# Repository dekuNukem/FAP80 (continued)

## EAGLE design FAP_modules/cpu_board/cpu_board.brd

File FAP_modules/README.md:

Here are all the schematic file, board file, and firmware of FAP's individual boards. Please see corresponding folders for details.

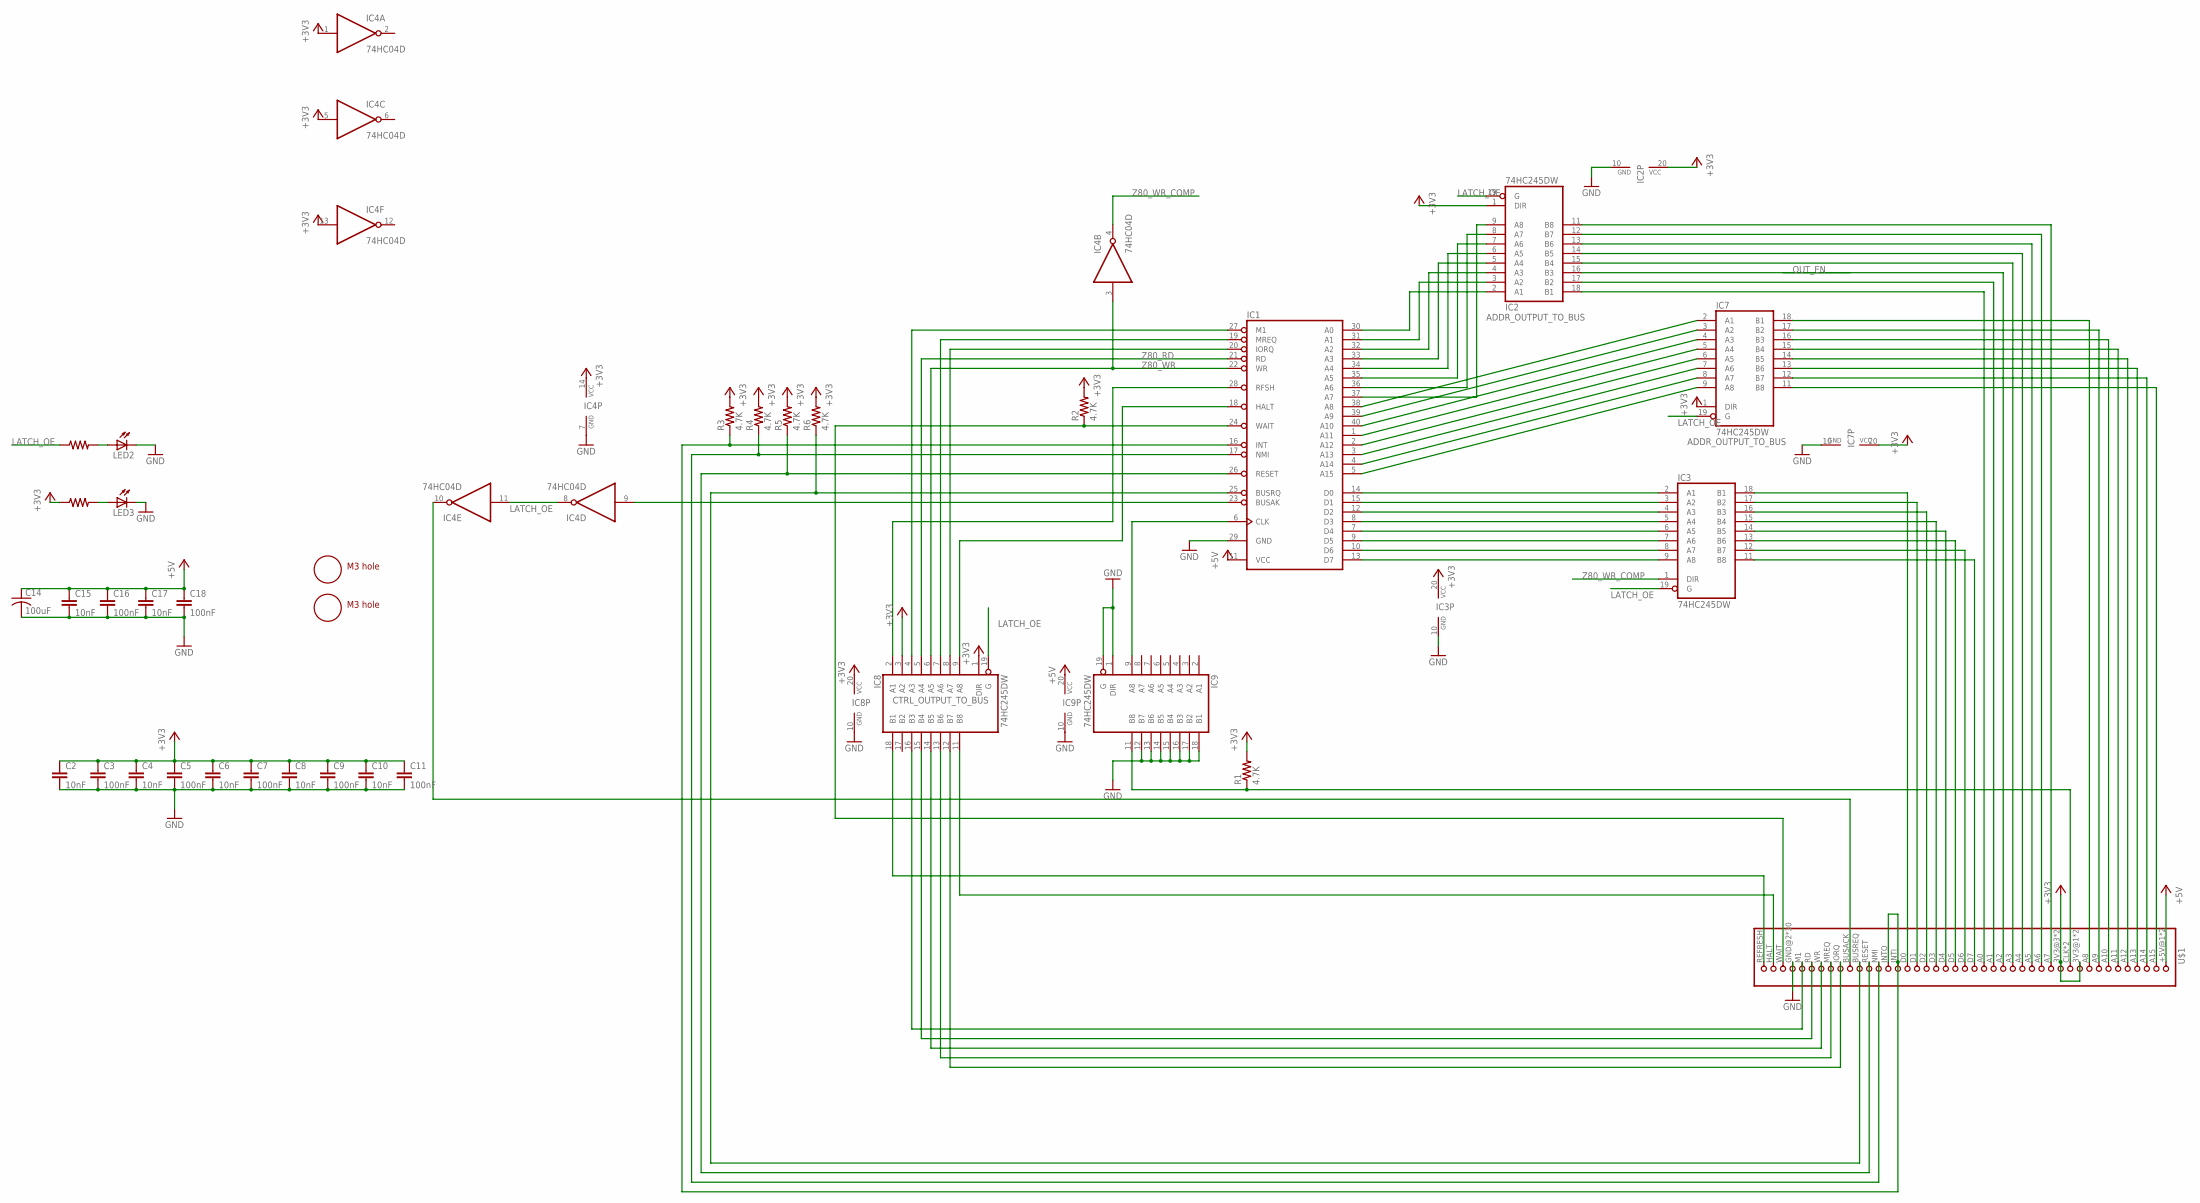
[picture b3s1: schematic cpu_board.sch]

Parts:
C2, C4, C6, C8, C10, C15, C17: 10nF; 0805
C3, C5, C7, C9, C11, C16, C18: 100nF; 0805
C14: 100uF; C1210
IC1: Z80CPU; DIL40
IC2, IC3, IC7, IC8, IC9: 74HC245DW; SO20W
IC4: 74HC04D; SO14
LED2, LED3: LEDCHIP-LED0805; CHIP-LED0805
R1, R2, R3, R4, R5, R6: 4.7K; 0805
R7, R8: 2K; 0805
U$1: FAP_BUS; 2X38
U$2, U$3: M3_MOUNTING_HOLE; M3_MOUNTING_HOLE_PACK

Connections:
+3V3: C2.1, C3.1, C4.1, C5.1, C6.1, C7.1, C8.1, C9.1, C10.1, C11.1, IC2.1 (DIR), IC2.20 (VCC), IC3.20 (VCC), IC4.1 (I), IC4.5 (I), IC4.13 (I), IC4.14 (VCC), IC7.1 (DIR), IC7.20 (VCC), IC8.1 (DIR), IC8.3 (A2), IC8.20 (VCC), R1.2, R2.2, R3.2, R4.2, R5.2, R6.2, R8.1, U$1.3V3@1 (10), U$1.3V3@2 (10), U$1.3V3@3 (12), U$1.3V3@4 (12)
+5V: C14.1, C15.1, C16.1, C17.1, C18.1, IC1.11 (VCC), IC9.20 (VCC), U$1.+5V@1 (1), U$1.+5V@2 (1)
GND: C2.2, C3.2, C4.2, C5.2, C6.2, C7.2, C8.2, C9.2, C10.2, C11.2, C14.2, C15.2, C16.2, C17.2, C18.2, IC1.29 (GND), IC2.10 (GND), IC3.10 (GND), IC4.7 (GND), IC7.10 (GND), IC8.10 (GND), IC9.1 (DIR), IC9.10 (GND), IC9.12 (B7), IC9.13 (B6), IC9.14 (B5), IC9.15 (B4), IC9.16 (B3), IC9.17 (B2), IC9.18 (B1), IC9.19 (G), LED2.C, LED3.C, U$1.GND@2 (GND), U$1.GND@3 (GND), U$1.GND@4 (GND), U$1.GND@5 (GND), U$1.GND@6 (GND), U$1.GND@7 (GND), U$1.GND@8 (GND), U$1.GND@9 (GND), U$1.GND@13 (GND), U$1.GND@14 (GND), U$1.GND@15 (GND), U$1.GND@16 (GND), U$1.GND@17 (GND), U$1.GND@18 (GND), U$1.GND@19 (GND), U$1.GND@20 (GND), U$1.GND@21 (GND), U$1.GND@22 (GND), U$1.GND@23 (GND), U$1.GND@24 (GND), U$1.GND@25 (GND), U$1.GND@26 (GND), U$1.GND@27 (GND), U$1.GND@28 (GND), U$1.GND@30 (GND), U$1.GND@34 (GND), U$1.GND@35 (GND), U$1.GND@36 (GND), U$1.GND@37 (GND), U$1.GND@38 (GND)
LATCH_OE: IC2.19 (G), IC3.19 (G), IC4.8 (O), IC4.11 (I), IC7.19 (G), IC8.19 (G), R7.1
unnamed: IC1.38 (A8), IC7.2 (A1)
unnamed: IC1.39 (A9), IC7.3 (A2)
unnamed: IC1.40 (A10), IC7.4 (A3)
unnamed: IC1.1 (A11), IC7.5 (A4)
unnamed: IC1.2 (A12), IC7.6 (A5)
unnamed: IC1.3 (A13), IC7.7 (A6)
unnamed: IC1.4 (A14), IC7.8 (A7)
unnamed: IC1.5 (A15), IC7.9 (A8)
unnamed: IC1.37 (A7), IC2.9 (A8)
unnamed: IC1.36 (A6), IC2.8 (A7)
unnamed: IC1.35 (A5), IC2.7 (A6)
unnamed: IC1.34 (A4), IC2.6 (A5)
unnamed: IC1.33 (A3), IC2.5 (A4)
unnamed: IC1.32 (A2), IC2.4 (A3)
unnamed: IC1.31 (A1), IC2.3 (A2)
unnamed: IC1.30 (A0), IC2.2 (A1)
unnamed: IC1.14 (D0), IC3.2 (A1)
unnamed: IC1.15 (D1), IC3.3 (A2)
unnamed: IC1.12 (D2), IC3.4 (A3)
unnamed: IC1.8 (D3), IC3.5 (A4)
unnamed: IC1.7 (D4), IC3.6 (A5)
unnamed: IC1.9 (D5), IC3.7 (A6)
unnamed: IC1.10 (D6), IC3.8 (A7)
unnamed: IC1.13 (D7), IC3.9 (A8)
unnamed: IC4.10 (O), U$1.BUSACK (33)
unnamed: IC9.11 (B8), R1.1, U$1.CLK (11), U$1.CLK@2 (11)
unnamed: IC1.6 (CLK), IC9.9 (A8)
unnamed: LED2.A, R7.2
unnamed: IC1.25 (BUSRQ), R6.1, U$1.BUSREQ (32)
unnamed: IC1.23 (BUSAK), IC4.9 (I)
unnamed: IC1.26 (RESET), R5.1, U$1.RESET (31)
unnamed: IC1.24 (WAIT), R2.1, U$1.WAIT (40)
unnamed: IC1.17 (NMI), R4.1, U$1.NMI (30)
unnamed: IC1.18 (HALT), IC8.9 (A8)
unnamed: IC1.16 (INT), R3.1, U$1.INTI (29), U$1.INTO (39)
unnamed: IC1.19 (MREQ), IC8.7 (A6)
unnamed: IC8.11 (B8), U$1.HALT (41)
unnamed: IC1.28 (RFSH), IC8.2 (A1)
unnamed: IC1.20 (IORQ), IC8.8 (A7)
unnamed: IC1.27 (M1), IC8.4 (A3)
unnamed: IC8.16 (B3), U$1.M1 (38)
unnamed: IC8.13 (B6), U$1.MREQ (35)
unnamed: IC8.15 (B4), U$1.RD (37)
unnamed: IC8.14 (B5), U$1.WR (36)
unnamed: IC8.12 (B7), U$1.IORQ (34)
unnamed: IC3.17 (B2), U$1.D1 (27)
unnamed: IC3.11 (B8), U$1.D7 (21)
unnamed: IC3.12 (B7), U$1.D6 (22)
unnamed: IC3.13 (B6), U$1.D5 (23)
unnamed: IC3.14 (B5), U$1.D4 (24)
unnamed: IC3.15 (B4), U$1.D3 (25)
unnamed: IC3.16 (B3), U$1.D2 (26)
unnamed: IC3.18 (B1), U$1.D0 (28)
unnamed: IC7.11 (B8), U$1.A15 (2)
unnamed: IC7.12 (B7), U$1.A14 (3)
unnamed: IC7.13 (B6), U$1.A13 (4)
unnamed: IC2.18 (B1), U$1.A0 (20)
unnamed: IC2.17 (B2), U$1.A1 (19)
unnamed: IC2.16 (B3), U$1.A2 (18)
unnamed: IC2.15 (B4), U$1.A3 (17)
unnamed: IC2.14 (B5), U$1.A4 (16)
unnamed: IC2.13 (B6), U$1.A5 (15)
unnamed: IC2.12 (B7), U$1.A6 (14)
unnamed: IC2.11 (B8), U$1.A7 (13)
unnamed: IC7.14 (B5), U$1.A12 (5)
unnamed: IC7.15 (B4), U$1.A11 (6)
unnamed: IC7.16 (B3), U$1.A10 (7)
unnamed: IC7.17 (B2), U$1.A9 (8)
unnamed: IC7.18 (B1), U$1.A8 (9)
unnamed: IC8.18 (B1), U$1.REFRESH (42)
unnamed: LED3.A, R8.2
Z80_RD: IC1.21 (RD), IC8.5 (A4)
Z80_WR: IC1.22 (WR), IC4.3 (I), IC8.6 (A5)
Z80_WR_COMP: IC3.1 (DIR), IC4.4 (O)

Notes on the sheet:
CTRL_OUTPUT_TO_BUS
ADDR_OUTPUT_TO_BUS

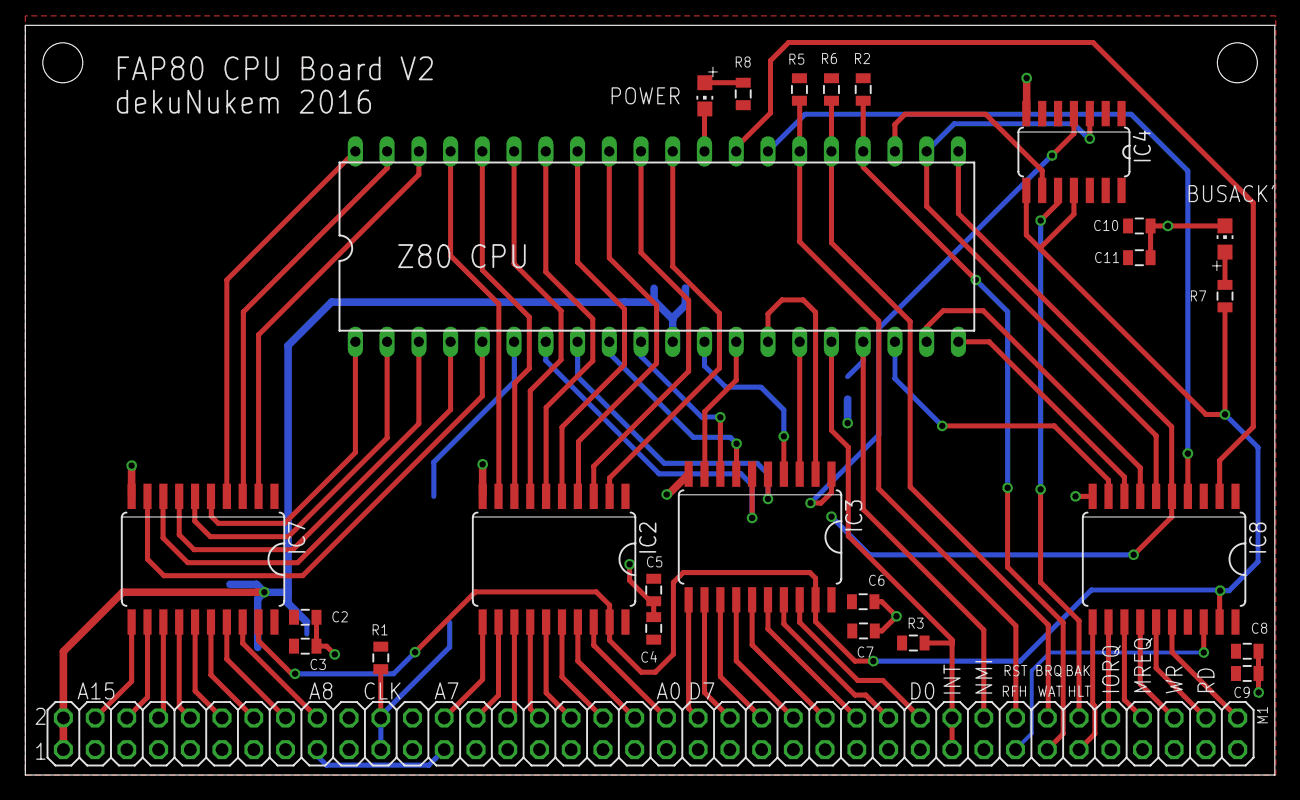
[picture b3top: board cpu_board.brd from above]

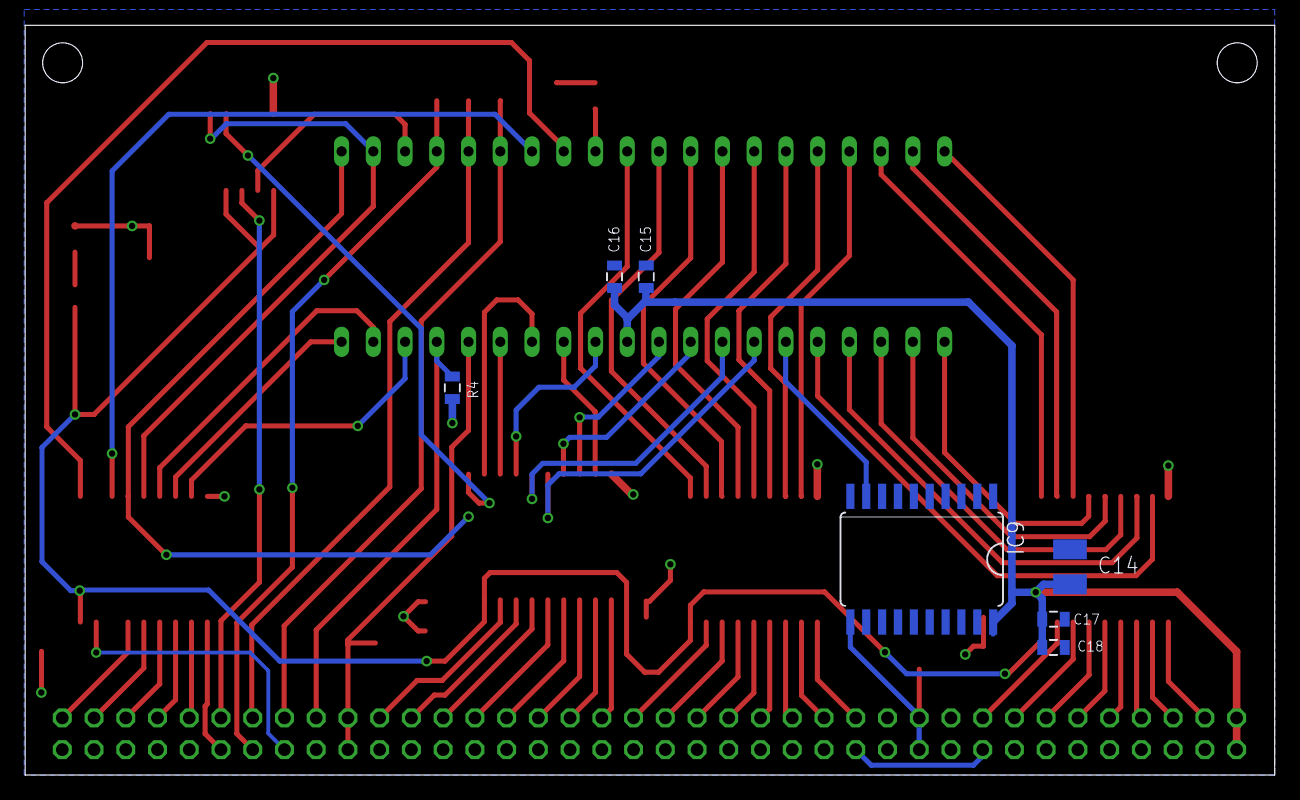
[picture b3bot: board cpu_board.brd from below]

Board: 2 copper layers, 100.0 x 60.0 mm, 35 parts (7 on the bottom side), 78 nets.

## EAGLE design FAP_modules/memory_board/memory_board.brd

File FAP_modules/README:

This folder holds the schematic, board file, and firmware of FAP's individual boards. Please see corresponding folders for source files.

This repo is still under consturction, more information will be added as I continute to add to the documentations and clean up the codebase.

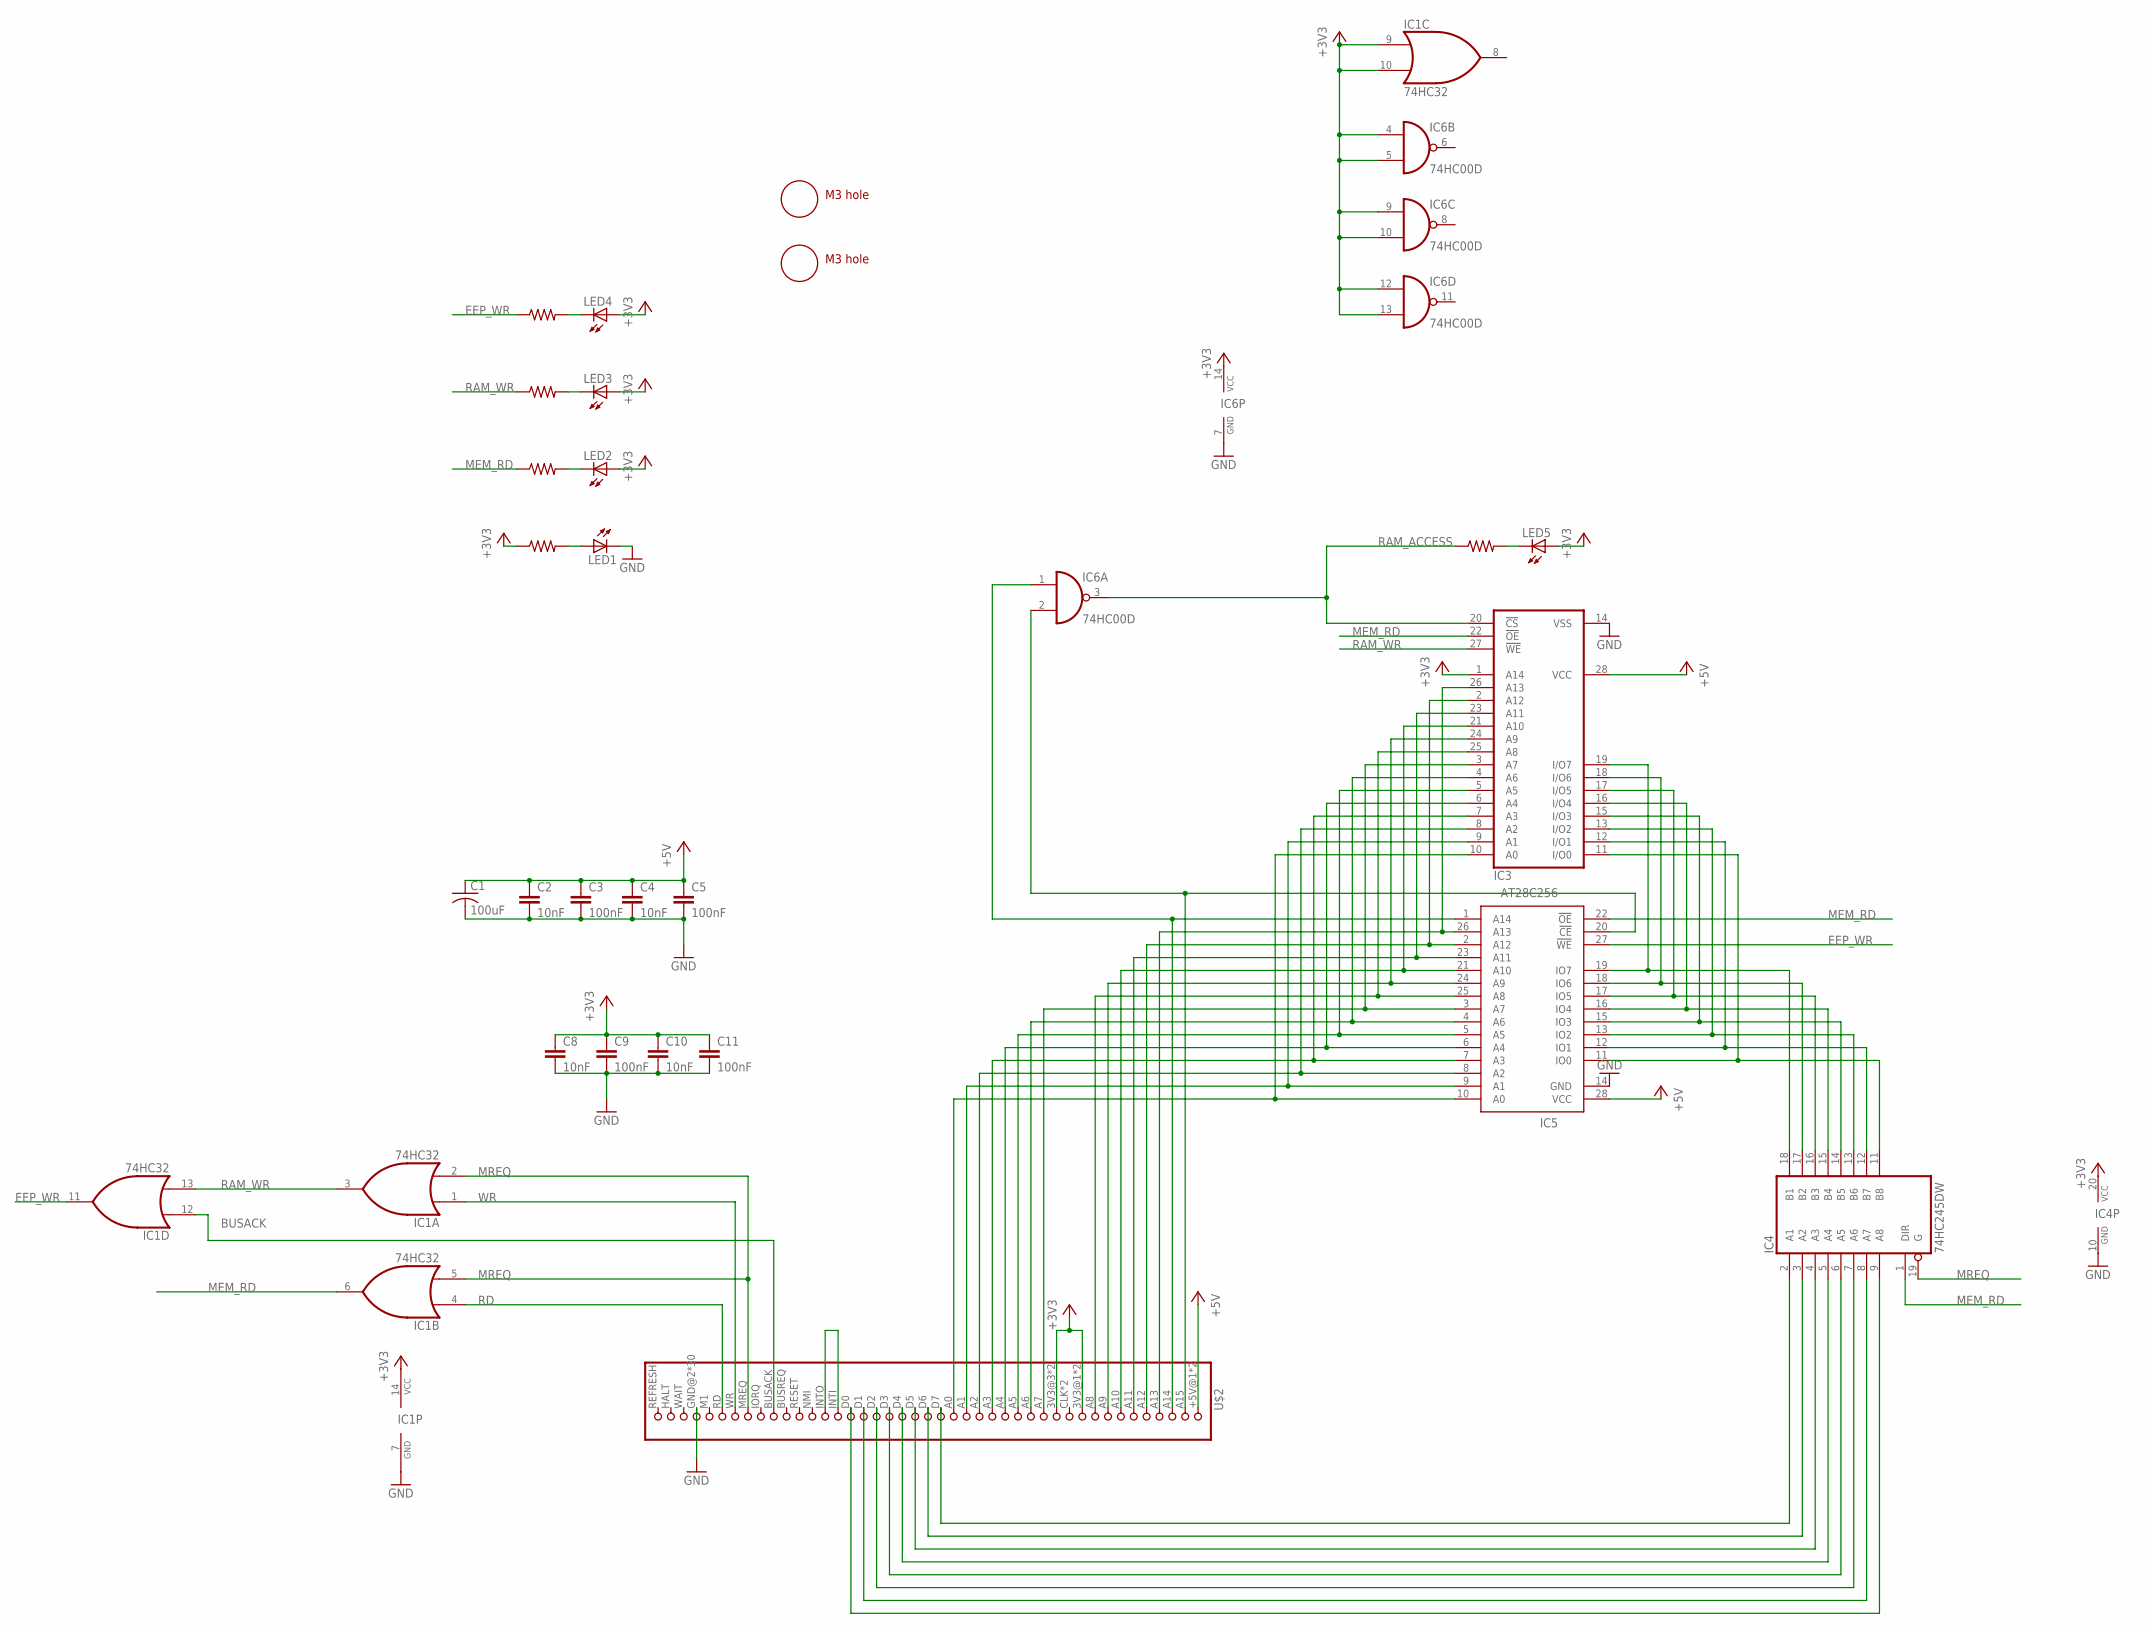
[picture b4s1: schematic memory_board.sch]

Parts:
C1: 100uF; C1210
C2, C4, C8, C10: 10nF; 0805
C3, C5, C9, C11: 100nF; 0805
IC1: 74HC32; SO14
IC3: 62256P; DIL28-6
IC4: 74HC245DW; SO20W
IC5: AT28C256; DIL28-6
IC6: 74HC00D; SO14
LED1, LED2, LED3, LED4, LED5: LEDCHIP-LED0805; CHIP-LED0805
R1, R2, R3, R7, R8: 2K; 0805
U$1, U$3: M3_MOUNTING_HOLE; M3_MOUNTING_HOLE_PACK
U$2: FAP_BUS; 2X38

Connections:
+3V3: C8.1, C9.1, C10.1, C11.1, IC1.9 (I0), IC1.10 (I1), IC1.14 (VCC), IC3.1 (A14), IC4.20 (VCC), IC6.4 (I0), IC6.5 (I1), IC6.9 (I0), IC6.10 (I1), IC6.12 (I0), IC6.13 (I1), IC6.14 (VCC), LED2.A, LED3.A, LED4.A, LED5.A, R8.1, U$2.3V3@1 (10), U$2.3V3@2 (10), U$2.3V3@3 (12), U$2.3V3@4 (12)
+5V: C1.1, C2.1, C3.1, C4.1, C5.1, IC3.28 (VCC), IC5.28 (VCC), U$2.+5V@1 (1), U$2.+5V@2 (1)
BUSACK: IC1.12 (I0), U$2.BUSACK (33)
EEP_WR: IC1.11 (O), IC5.27 (!WE), R2.1
GND: C1.2, C2.2, C3.2, C4.2, C5.2, C8.2, C9.2, C10.2, C11.2, IC1.7 (GND), IC3.14 (VSS), IC4.10 (GND), IC5.14 (GND), IC6.7 (GND), LED1.C, U$2.GND@2 (GND), U$2.GND@3 (GND), U$2.GND@4 (GND), U$2.GND@5 (GND), U$2.GND@6 (GND), U$2.GND@7 (GND), U$2.GND@8 (GND), U$2.GND@9 (GND), U$2.GND@13 (GND), U$2.GND@14 (GND), U$2.GND@15 (GND), U$2.GND@16 (GND), U$2.GND@17 (GND), U$2.GND@18 (GND), U$2.GND@19 (GND), U$2.GND@20 (GND), U$2.GND@21 (GND), U$2.GND@22 (GND), U$2.GND@23 (GND), U$2.GND@24 (GND), U$2.GND@25 (GND), U$2.GND@26 (GND), U$2.GND@27 (GND), U$2.GND@28 (GND), U$2.GND@30 (GND), U$2.GND@34 (GND), U$2.GND@35 (GND), U$2.GND@36 (GND), U$2.GND@37 (GND), U$2.GND@38 (GND)
MEM_RD: IC1.6 (O), IC3.22 (!OE), IC4.1 (DIR), IC5.22 (!OE), R7.1
MREQ: IC1.2 (I1), IC1.5 (I1), IC4.19 (G), U$2.MREQ (35)
unnamed: IC3.19 (I/O7), IC4.18 (B1), IC5.19 (IO7)
unnamed: IC3.18 (I/O6), IC4.17 (B2), IC5.18 (IO6)
unnamed: IC3.17 (I/O5), IC4.16 (B3), IC5.17 (IO5)
unnamed: IC3.16 (I/O4), IC4.15 (B4), IC5.16 (IO4)
unnamed: IC3.15 (I/O3), IC4.14 (B5), IC5.15 (IO3)
unnamed: IC3.13 (I/O2), IC4.13 (B6), IC5.13 (IO2)
unnamed: IC3.12 (I/O1), IC4.12 (B7), IC5.12 (IO1)
unnamed: IC3.11 (I/O0), IC4.11 (B8), IC5.11 (IO0)
unnamed: IC5.1 (A14), IC6.1 (I0), U$2.A14 (3)
unnamed: IC3.26 (A13), IC5.26 (A13), U$2.A13 (4)
unnamed: IC3.2 (A12), IC5.2 (A12), U$2.A12 (5)
unnamed: IC3.23 (A11), IC5.23 (A11), U$2.A11 (6)
unnamed: IC3.21 (A10), IC5.21 (A10), U$2.A10 (7)
unnamed: IC3.24 (A9), IC5.24 (A9), U$2.A9 (8)
unnamed: IC3.25 (A8), IC5.25 (A8), U$2.A8 (9)
unnamed: IC3.3 (A7), IC5.3 (A7), U$2.A7 (13)
unnamed: IC3.4 (A6), IC5.4 (A6), U$2.A6 (14)
unnamed: IC3.5 (A5), IC5.5 (A5), U$2.A5 (15)
unnamed: IC3.6 (A4), IC5.6 (A4), U$2.A4 (16)
unnamed: IC3.7 (A3), IC5.7 (A3), U$2.A3 (17)
unnamed: IC3.8 (A2), IC5.8 (A2), U$2.A2 (18)
unnamed: IC3.9 (A1), IC5.9 (A1), U$2.A1 (19)
unnamed: IC3.10 (A0), IC5.10 (A0), U$2.A0 (20)
unnamed: IC4.9 (A8), U$2.D0 (28)
unnamed: IC4.8 (A7), U$2.D1 (27)
unnamed: IC4.7 (A6), U$2.D2 (26)
unnamed: IC4.6 (A5), U$2.D3 (25)
unnamed: IC4.5 (A4), U$2.D4 (24)
unnamed: IC4.4 (A3), U$2.D5 (23)
unnamed: IC4.3 (A2), U$2.D6 (22)
unnamed: IC4.2 (A1), U$2.D7 (21)
unnamed: IC5.20 (!CE), IC6.2 (I1), U$2.A15 (2)
unnamed: U$2.INTI (29), U$2.INTO (39)
unnamed: LED2.C, R7.2
unnamed: LED3.C, R1.2
unnamed: LED4.C, R2.2
unnamed: LED5.C, R3.2
unnamed: LED1.A, R8.2
RAM_ACCESS: IC3.20 (!CS), IC6.3 (O), R3.1
RAM_WR: IC1.3 (O), IC1.13 (I1), IC3.27 (!WE), R1.1
RD: IC1.4 (I0), U$2.RD (37)
WR: IC1.1 (I0), U$2.WR (36)

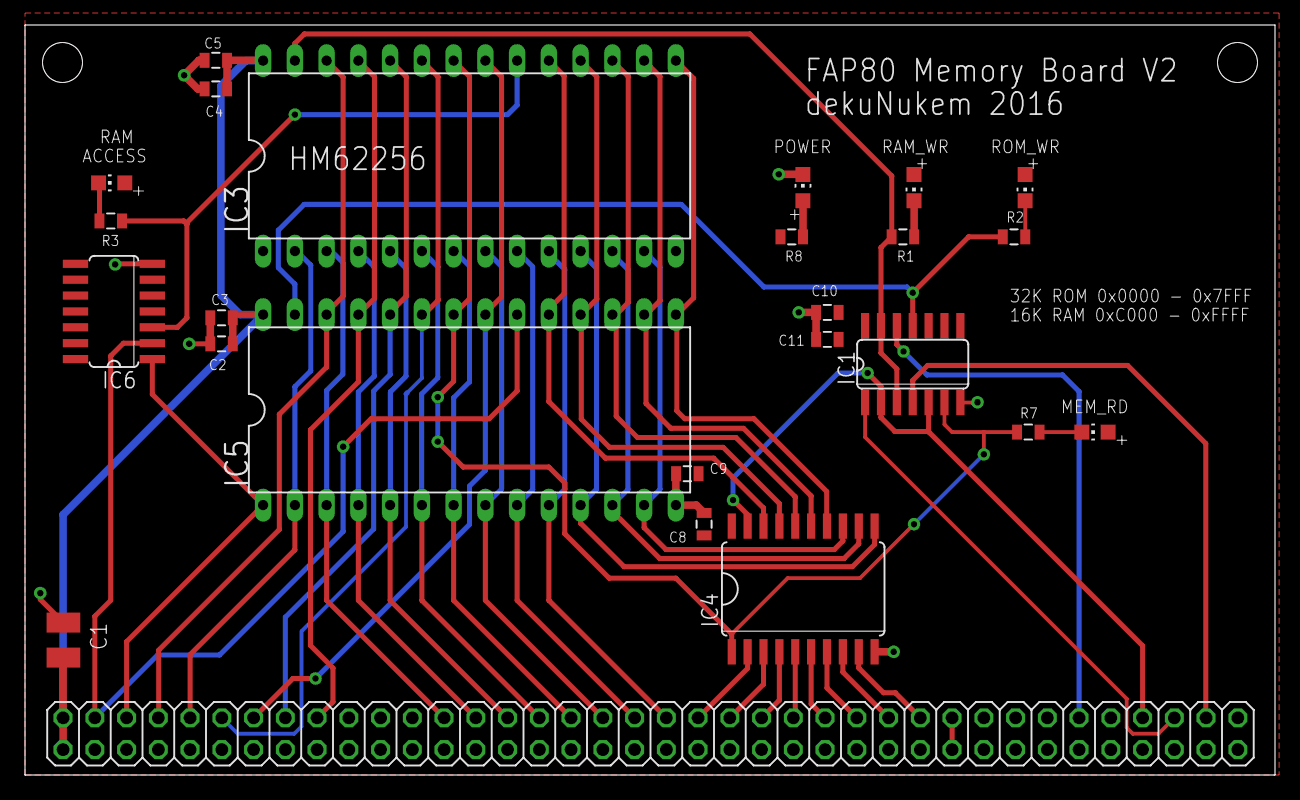
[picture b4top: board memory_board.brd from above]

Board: 2 copper layers, 100.0 x 60.0 mm, 27 parts (0 on the bottom side), 49 nets.

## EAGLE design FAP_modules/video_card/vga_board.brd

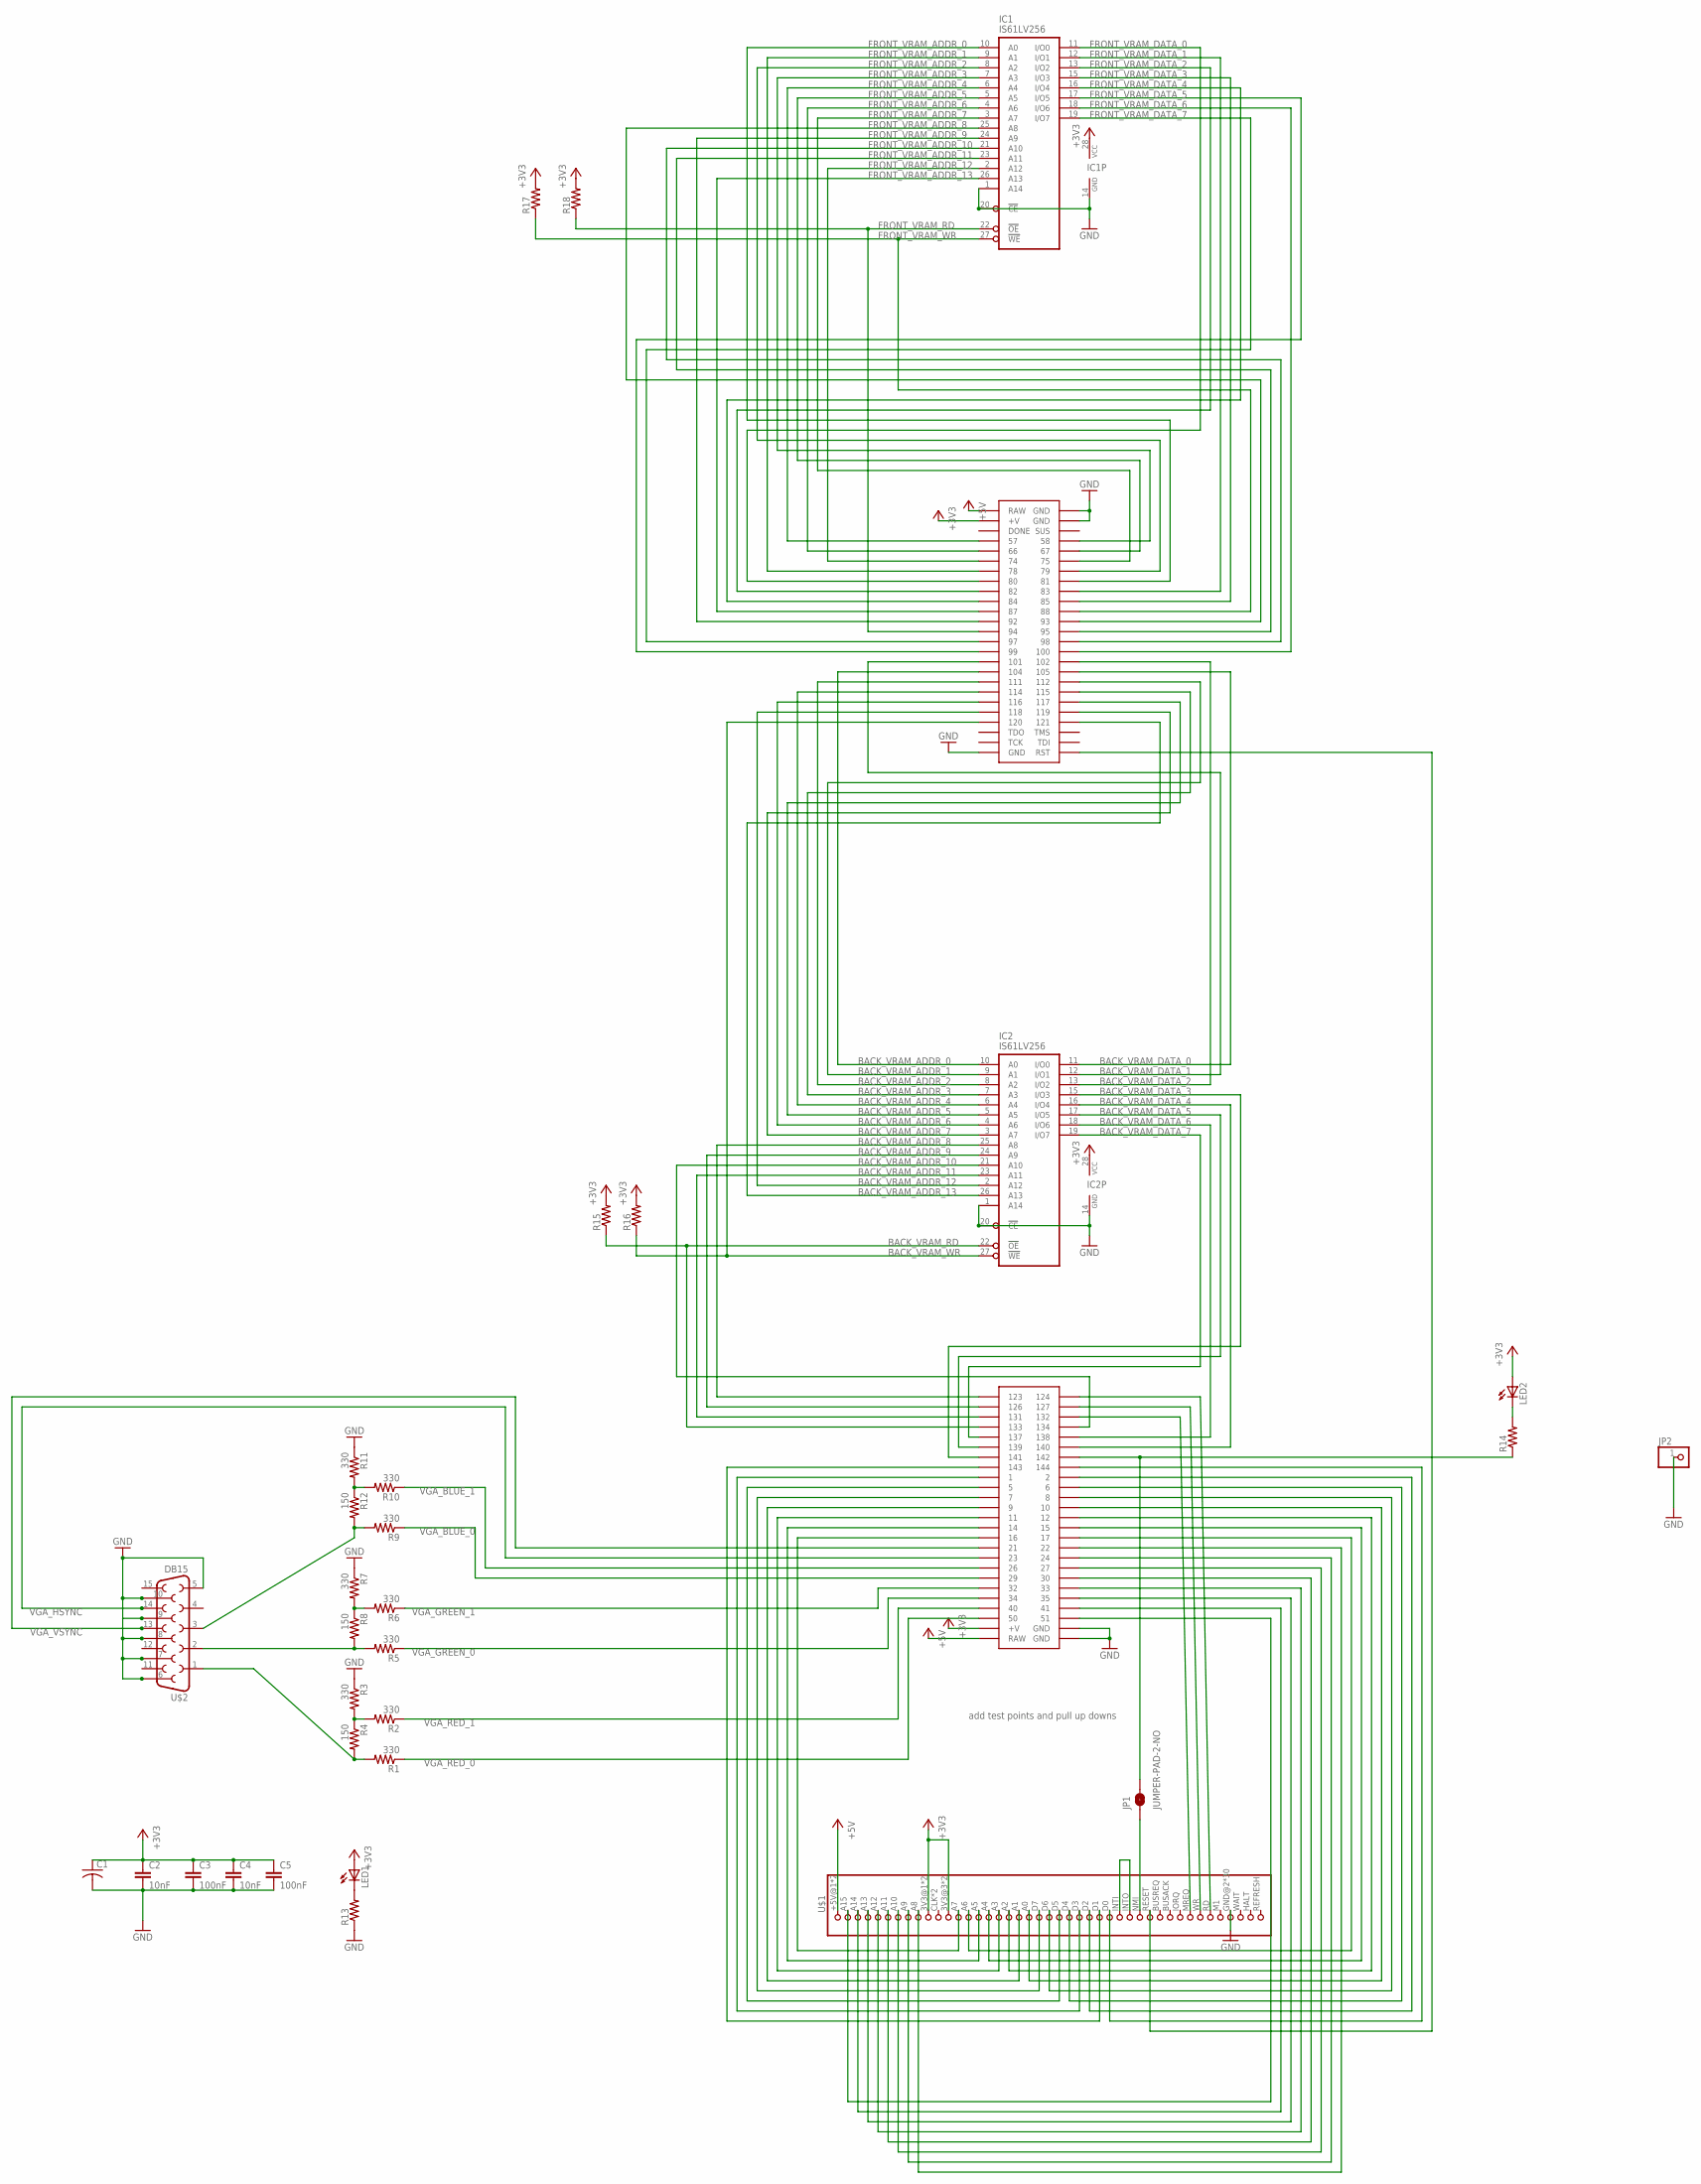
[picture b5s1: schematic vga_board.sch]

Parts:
C1: C-USC1210; C1210
C2, C4: 10nF; 0805
C3, C5: 100nF; 0805
IC1, IC2: IS61LV256; SOJ28/3_LONGPAD
JP1: JUMPER-PAD-2-NO; PAD-JUMPER-2-NO_NO_SILK
JP2: PINHD-1X1; 1X01
LED1, LED2: LEDCHIP-LED0805; CHIP-LED0805
R1, R2, R3, R5, R6, R7, R9, R10, R11: 330; 0805
R4, R8, R12: 150; 0805
R13, R14, R15, R16, R17, R18: RESISTOR0805-RES; 0805
U$1: FAP_BUS; 2X38
U$2: DB15
U$3: MOJOV3_NO_LABEL; MOJO_V3_NO_LABEL

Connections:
+3V3: C1.1, C2.1, C3.1, C4.1, C5.1, IC1.28 (VCC), IC2.28 (VCC), LED1.A, LED2.A, R15.2, R16.2, R17.2, R18.2, U$1.3V3@1 (10), U$1.3V3@2 (10), U$1.3V3@3 (12), U$1.3V3@4 (12), U$3.V@1 (+V)
+5V: U$1.+5V@1 (1), U$1.+5V@2 (1), U$3.RAW@1 (RAW)
+V: U$3.V@2 (+V)
BACK_VRAM_ADDR_0: IC2.10 (A0), U$3.104
BACK_VRAM_ADDR_1: IC2.9 (A1), U$3.112
BACK_VRAM_ADDR_2: IC2.8 (A2), U$3.111
BACK_VRAM_ADDR_3: IC2.7 (A3), U$3.115
BACK_VRAM_ADDR_4: IC2.6 (A4), U$3.114
BACK_VRAM_ADDR_5: IC2.5 (A5), U$3.117
BACK_VRAM_ADDR_6: IC2.4 (A6), U$3.116
BACK_VRAM_ADDR_7: IC2.3 (A7), U$3.119
BACK_VRAM_ADDR_8: IC2.25 (A8), U$3.123
BACK_VRAM_ADDR_9: IC2.24 (A9), U$3.126
BACK_VRAM_ADDR_10: IC2.21 (A10), U$3.134
BACK_VRAM_ADDR_11: IC2.23 (A11), U$3.131
BACK_VRAM_ADDR_12: IC2.2 (A12), U$3.118
BACK_VRAM_ADDR_13: IC2.26 (A13), U$3.121
BACK_VRAM_DATA_0: IC2.11 (I/O0), U$3.105
BACK_VRAM_DATA_1: IC2.12 (I/O1), U$3.101
BACK_VRAM_DATA_2: IC2.13 (I/O2), U$3.102
BACK_VRAM_DATA_3: IC2.15 (I/O3), U$3.141
BACK_VRAM_DATA_4: IC2.16 (I/O4), U$3.140
BACK_VRAM_DATA_5: IC2.17 (I/O5), U$3.139
BACK_VRAM_DATA_6: IC2.18 (I/O6), U$3.138
BACK_VRAM_DATA_7: IC2.19 (I/O7), U$3.137
BACK_VRAM_RD: IC2.22 (!OE), R15.1, U$3.133
BACK_VRAM_WR: IC2.27 (!WE), R16.1, U$3.120
FRONT_VRAM_ADDR_0: IC1.10 (A0), U$3.81
FRONT_VRAM_ADDR_1: IC1.9 (A1), U$3.78
FRONT_VRAM_ADDR_2: IC1.8 (A2), U$3.79
FRONT_VRAM_ADDR_3: IC1.7 (A3), U$3.58
FRONT_VRAM_ADDR_4: IC1.6 (A4), U$3.57
FRONT_VRAM_ADDR_5: IC1.5 (A5), U$3.67
FRONT_VRAM_ADDR_6: IC1.4 (A6), U$3.66
FRONT_VRAM_ADDR_7: IC1.3 (A7), U$3.75
FRONT_VRAM_ADDR_8: IC1.25 (A8), U$3.93
FRONT_VRAM_ADDR_9: IC1.24 (A9), U$3.92
FRONT_VRAM_ADDR_10: IC1.21 (A10), U$3.98
FRONT_VRAM_ADDR_11: IC1.23 (A11), U$3.95
FRONT_VRAM_ADDR_12: IC1.2 (A12), U$3.74
FRONT_VRAM_ADDR_13: IC1.26 (A13), U$3.87
FRONT_VRAM_DATA_0: IC1.11 (I/O0), U$3.80
FRONT_VRAM_DATA_1: IC1.12 (I/O1), U$3.83
FRONT_VRAM_DATA_2: IC1.13 (I/O2), U$3.82
FRONT_VRAM_DATA_3: IC1.15 (I/O3), U$3.85
FRONT_VRAM_DATA_4: IC1.16 (I/O4), U$3.84
FRONT_VRAM_DATA_5: IC1.17 (I/O5), U$3.99
FRONT_VRAM_DATA_6: IC1.18 (I/O6), U$3.100
FRONT_VRAM_DATA_7: IC1.19 (I/O7), U$3.97
FRONT_VRAM_RD: IC1.22 (!OE), R18.1, U$3.94
FRONT_VRAM_WR: IC1.27 (!WE), R17.1, U$3.88
GND: C1.2, C2.2, C3.2, C4.2, C5.2, IC1.1 (A14), IC1.14 (GND), IC1.20 (!CE), IC2.1 (A14), IC2.14 (GND), IC2.20 (!CE), JP2.1, R3.1, R7.1, R11.1, R13.1, U$1.GND@2 (GND), U$1.GND@3 (GND), U$1.GND@4 (GND), U$1.GND@5 (GND), U$1.GND@6 (GND), U$1.GND@7 (GND), U$1.GND@8 (GND), U$1.GND@9 (GND), U$1.GND@13 (GND), U$1.GND@14 (GND), U$1.GND@15 (GND), U$1.GND@16 (GND), U$1.GND@17 (GND), U$1.GND@18 (GND), U$1.GND@19 (GND), U$1.GND@20 (GND), U$1.GND@21 (GND), U$1.GND@22 (GND), U$1.GND@23 (GND), U$1.GND@24 (GND), U$1.GND@25 (GND), U$1.GND@26 (GND), U$1.GND@27 (GND), U$1.GND@28 (GND), U$1.GND@30 (GND), U$1.GND@34 (GND), U$1.GND@35 (GND), U$1.GND@36 (GND), U$1.GND@37 (GND), U$1.GND@38 (GND), U$2.5, U$2.6, U$2.7, U$2.8, U$2.9, U$2.10, U$3.GND@1 (GND), U$3.GND@2 (GND), U$3.GND@3 (GND), U$3.GND@4 (GND), U$3.GND@6 (GND)
unnamed: R2.2, R3.2, R4.1
unnamed: R1.2, R4.2, U$2.1
unnamed: R6.2, R7.2, R8.1
unnamed: R5.2, R8.2, U$2.2
unnamed: R10.2, R11.2, R12.1
unnamed: R9.2, R12.2, U$2.3
unnamed: U$1.A15 (2), U$3.51
unnamed: U$1.A14 (3), U$3.41
unnamed: U$1.A13 (4), U$3.35
unnamed: U$1.A12 (5), U$3.33
unnamed: U$1.RD (37), U$3.124
unnamed: U$1.WR (36), U$3.127
unnamed: U$1.MREQ (35), U$3.132
unnamed: U$1.A11 (6), U$3.30
unnamed: U$1.A10 (7), U$3.27
unnamed: U$1.A9 (8), U$3.24
unnamed: U$1.A8 (9), U$3.22
unnamed: U$1.A7 (13), U$3.16
unnamed: U$1.A6 (14), U$3.17
unnamed: U$1.A5 (15), U$3.14
unnamed: U$1.A4 (16), U$3.15
unnamed: U$1.A3 (17), U$3.11
unnamed: U$1.A2 (18), U$3.12
unnamed: U$1.A1 (19), U$3.9
unnamed: U$1.A0 (20), U$3.10
unnamed: U$1.D7 (21), U$3.7
unnamed: U$1.D6 (22), U$3.8
unnamed: U$1.D5 (23), U$3.5
unnamed: U$1.D4 (24), U$3.6
unnamed: U$1.D3 (25), U$3.1
unnamed: U$1.D2 (26), U$3.2
unnamed: U$1.D1 (27), U$3.143
unnamed: U$1.D0 (28), U$3.144
unnamed: LED1.C, R13.2
unnamed: LED2.C, R14.2
unnamed: JP1.2, R14.1, U$3.142
unnamed: U$1.RESET (31), U$3.RST
unnamed: U$1.INTI (29), U$1.INTO (39)
unnamed: JP1.1, U$1.NMI (30)
RAW: U$3.RAW@2 (RAW)
VGA_BLUE_0: R9.1, U$3.29
VGA_BLUE_1: R10.1, U$3.26
VGA_GREEN_0: R5.1, U$3.34
VGA_GREEN_1: R6.1, U$3.32
VGA_HSYNC: U$2.14, U$3.23
VGA_RED_0: R1.1, U$3.50
VGA_RED_1: R2.1, U$3.40
VGA_VSYNC: U$2.13, U$3.21

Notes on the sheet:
add test points and pull up downs

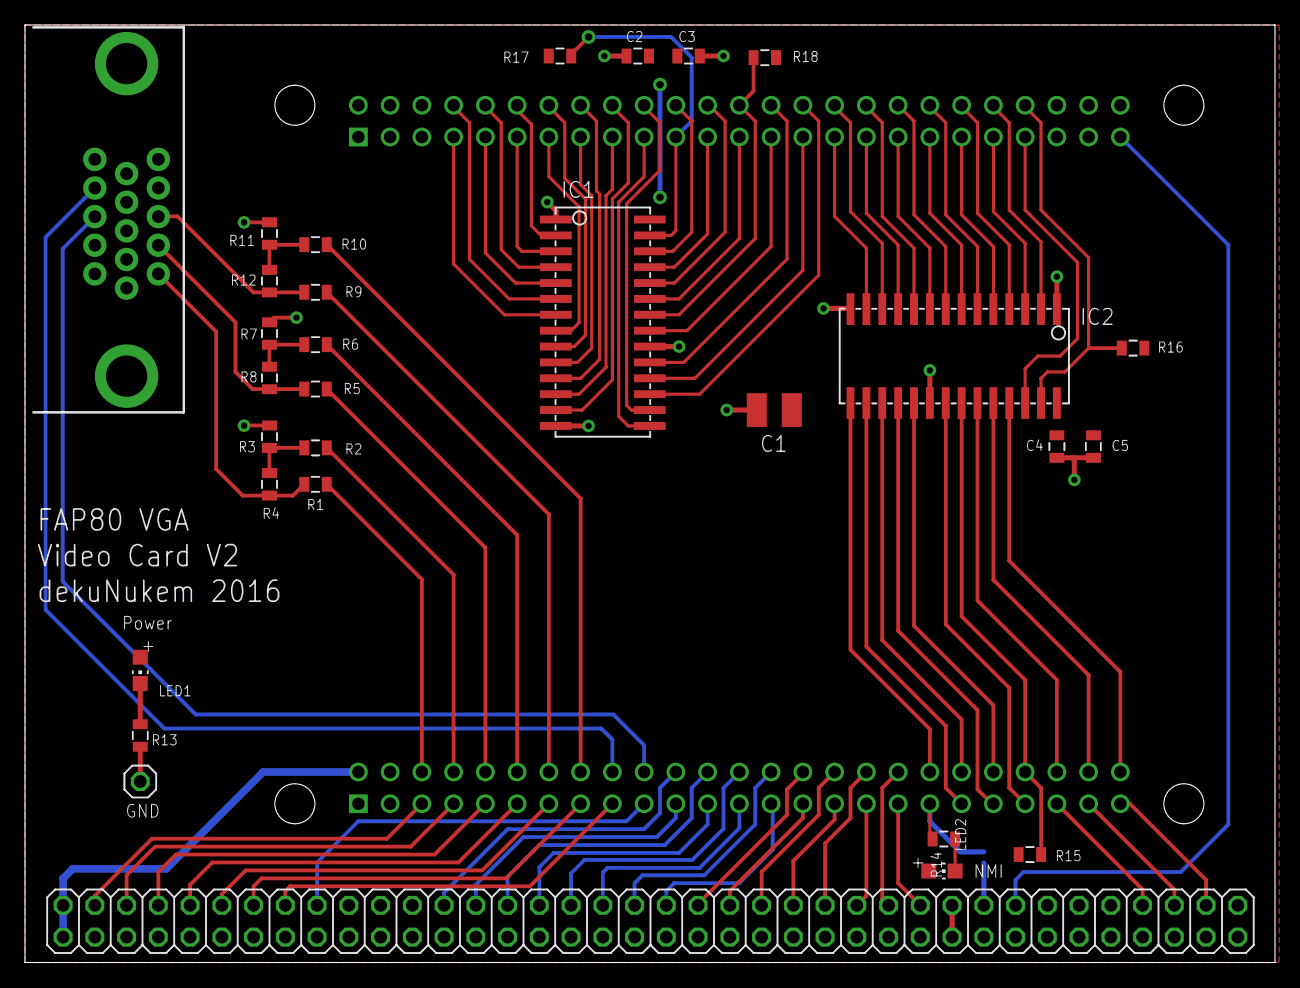
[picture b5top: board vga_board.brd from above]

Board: 2 copper layers, 100.0 x 75.0 mm, 32 parts (1 on the bottom side), 98 nets.

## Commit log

2016-12-18 wtf is happening
2016-12-18 test
2016-12-18 test2
2016-12-18 added placeholder
2016-12-18 first major commit
2016-12-18 added placeholder READMEs
2016-12-18 added asm examples
2016-12-18 more datasheets
2016-12-19 ported to latest HAL lib, pad byte set to 0xff
2016-12-19 added GND test headers
2016-12-19 header image
2016-12-19 building README
2016-12-19 updated with correct VGA FPGA code
2016-12-19 vga pcb trace fix
2016-12-20 code cleanup
2016-12-21 added interrupt chaining and WAIT
2016-12-21 moved VGA sockect
2016-12-21 WAIT and interrupt chaining on IO board
2016-12-21 fix JTAG pinout
2016-12-21 pcb cleanup
2016-12-21 new memory board
2016-12-21 board cleanup
2016-12-22 added all Z80 signals on bus
2016-12-22 updated README for new bus signals
2016-12-24 new clean script
2016-12-24 readme update
2016-12-25 io board cleanup
2016-12-25 rewrote 4to16 decoder verilog code
2016-12-25 io board stm32 code cleanup
2016-12-26 sdcc first commit
2016-12-26 connected BUSREQ to CPLD DEV_OE
2016-12-26 doc update
2016-12-26 update getting started guide
2016-12-26 update program guide
2016-12-26 clean.sh deletes ds_store
2016-12-30 updated firmware for new boards
2017-01-03 zmac test
2017-01-04 firmware updates
2017-01-04 added fapirc
2017-01-04 updated board pictures
2017-01-05 updated progress
2017-01-06 fixed image link
2017-01-20 added blog link
2017-01-23 fixed dead links
2017-04-06 fixed a type
